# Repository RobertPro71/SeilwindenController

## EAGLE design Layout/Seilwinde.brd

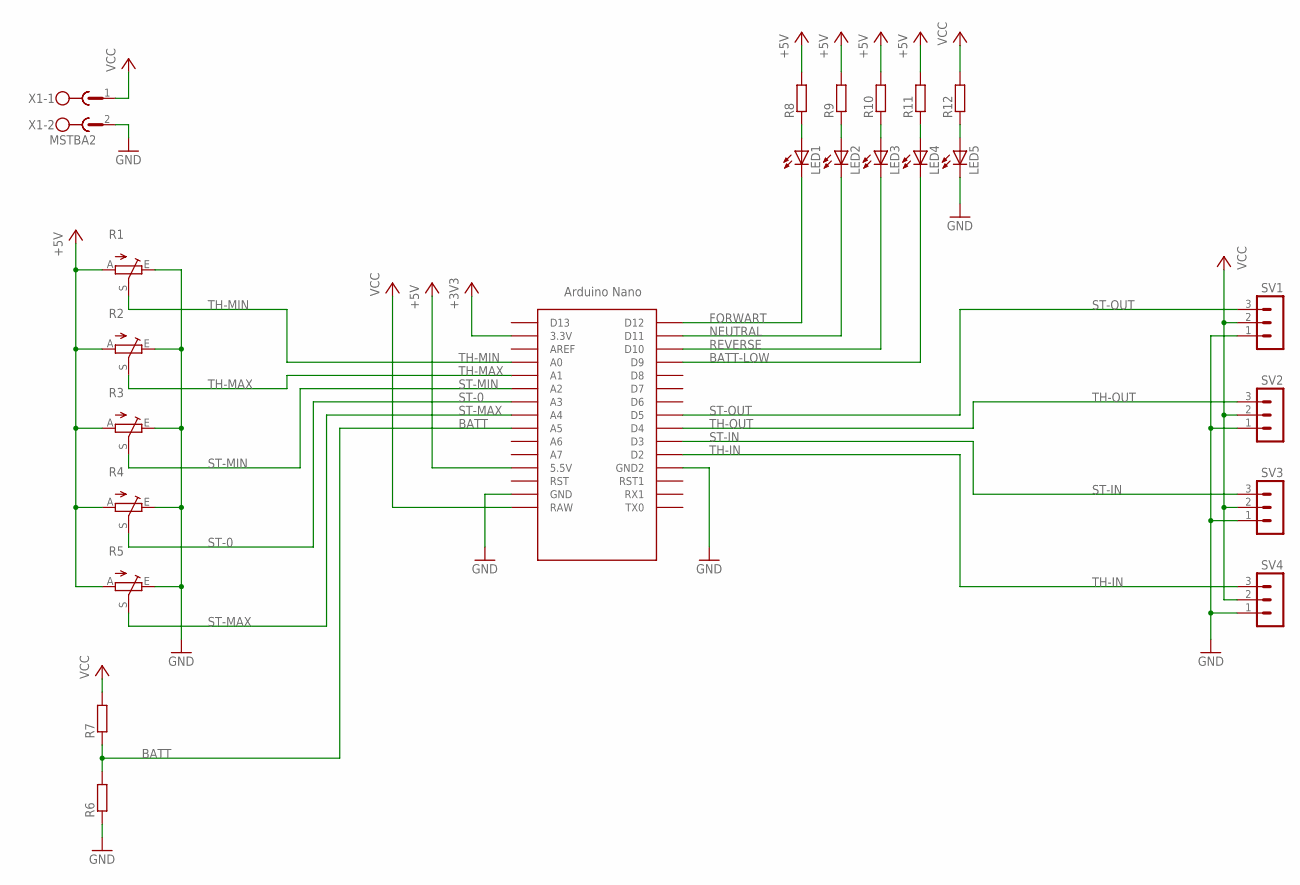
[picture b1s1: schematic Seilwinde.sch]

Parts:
LED1, LED2, LED3, LED4, LED5: LEDCHIPLED_1206; CHIPLED_1206
R1, R2, R3, R4, R5: TRIM_EU-S64W; S64W
R6, R7, R8, R9, R10, R11, R12: R-EU_R1206; R1206
SV1, SV2, SV3, SV4: MA03-1
U$1: NANO
X1: MSTBA2

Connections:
+3V3: U$1.3.3V
+5V: R1.A, R2.A, R3.A, R4.A, R5.A, R8.2, R9.2, R10.2, R11.2, U$1.5V (5.5V)
BATT: R6.2, R7.1, U$1.A5
BATT-LOW: LED4.C, U$1.D9
FORWART: LED1.C, U$1.D12
GND: LED5.C, R1.E, R2.E, R3.E, R4.E, R5.E, R6.1, SV1.1, SV2.1, SV3.1, SV4.1, U$1.GND, U$1.GND1 (GND2), X1.2
unnamed: LED5.A, R12.1
unnamed: LED1.A, R8.1
unnamed: LED2.A, R9.1
unnamed: LED3.A, R10.1
unnamed: LED4.A, R11.1
NEUTRAL: LED2.C, U$1.D11
REVERSE: LED3.C, U$1.D10
ST-0: R4.S, U$1.A3
ST-IN: SV3.3, U$1.D3
ST-MAX: R5.S, U$1.A4
ST-MIN: R3.S, U$1.A2
ST-OUT: SV1.3, U$1.D5
TH-IN: SV4.3, U$1.D2
TH-MAX: R2.S, U$1.A1
TH-MIN: R1.S, U$1.A0
TH-OUT: SV2.3, U$1.D4
VCC: R7.2, R12.2, SV1.2, SV2.2, SV3.2, SV4.2, U$1.RAW, X1.1

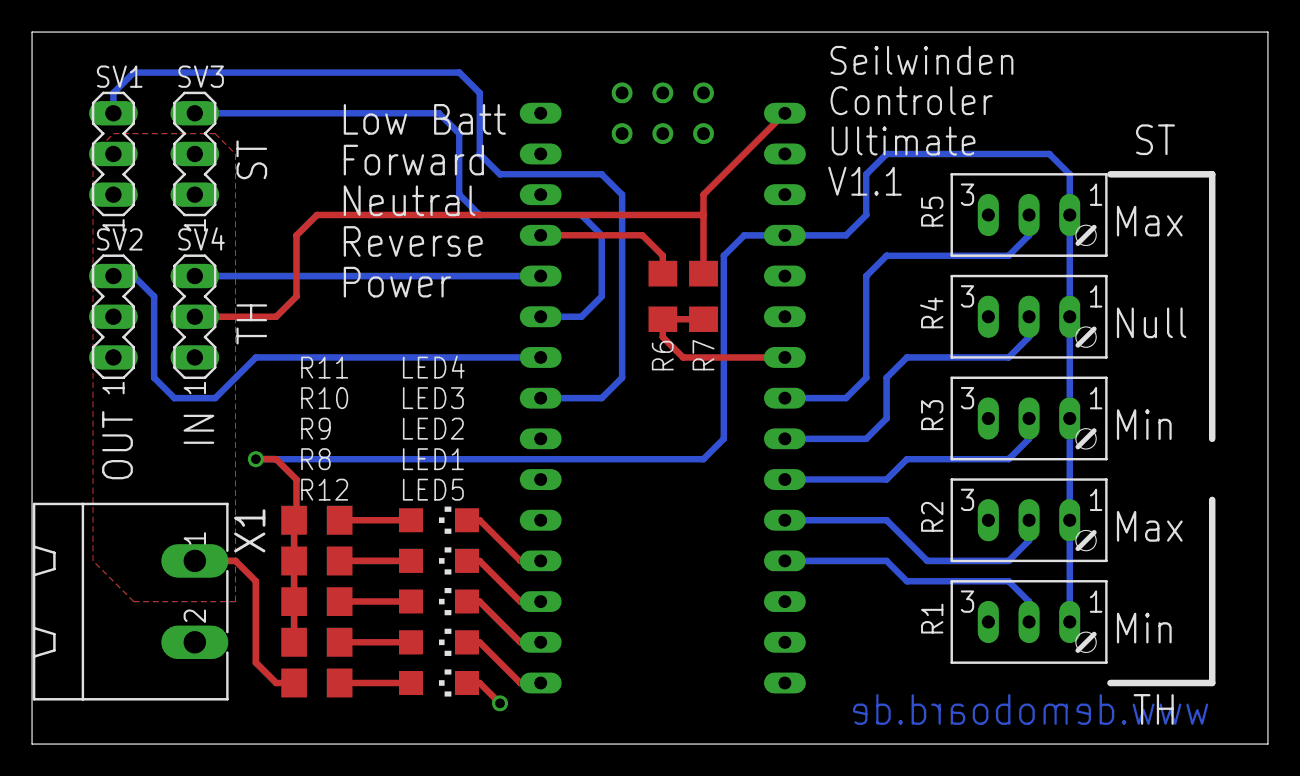
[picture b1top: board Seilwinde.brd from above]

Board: 2 copper layers, 77.1 x 44.4 mm, 23 parts (0 on the bottom side), 22 nets.

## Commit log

2018-07-08 Handle PPM input ready but untested
2018-07-12 Erkennung läuft aber Steuern nicht.
2018-07-30 Not working, only for transfer
2019-06-18 Now working
2019-06-18 some comment
2019-09-05 Keine Ahnung, zu lange her.
2019-09-09 Beta Release
